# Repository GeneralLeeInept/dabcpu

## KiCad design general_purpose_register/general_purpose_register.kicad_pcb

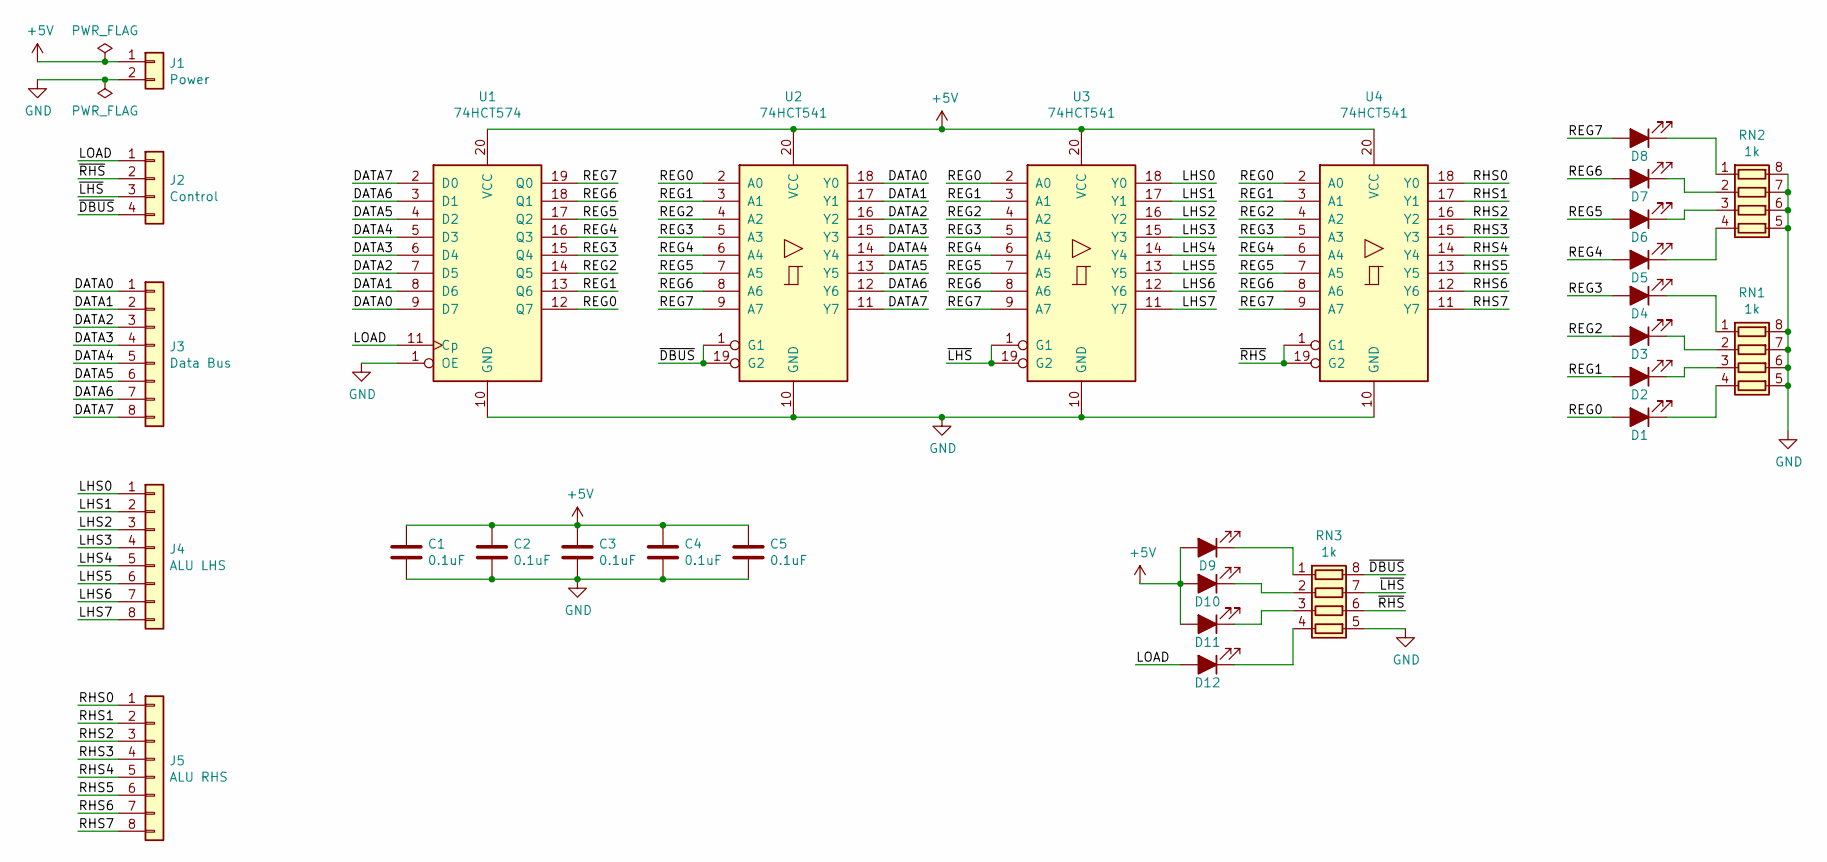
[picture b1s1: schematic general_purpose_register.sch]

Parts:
C1, C2, C3, C4, C5: 0.1uF; C_0805_2012Metric_Pad1.18x1.45mm_HandSolder
D1, D2, D3, D4, D5, D6, D7, D8, D9, D10, D11, D12: LED_ALT; LED_0805_2012Metric_Pad1.15x1.40mm_HandSolder
J1: Power; PinHeader_1x02_P2.54mm_Vertical
J2: Control; PinHeader_1x04_P2.54mm_Vertical
J3: Data Bus; PinHeader_1x08_P2.54mm_Vertical
J4: ALU LHS; PinHeader_1x08_P2.54mm_Vertical
J5: ALU RHS; PinHeader_1x08_P2.54mm_Vertical
RN1, RN2, RN3: 1k; R_Array_Convex_4x1206
U1: 74HCT574; SOIC-20W_7.5x12.8mm_P1.27mm; digikey 1727-2856-1-ND
U2, U3, U4: 74HCT541; SOIC-20W_7.5x12.8mm_P1.27mm; digikey 1727-6357-1-ND

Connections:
+5V: C1.1, C2.1, C3.1, C4.1, C5.1, D9.2 (A), D10.2 (A), D11.2 (A), J1.1, U1.20 (VCC), U2.20 (VCC), U3.20 (VCC), U4.20 (VCC)
/DATA0: J3.1, U1.9 (D7), U2.18 (Y0)
/DATA1: J3.2, U1.8 (D6), U2.17 (Y1)
/DATA2: J3.3, U1.7 (D5), U2.16 (Y2)
/DATA3: J3.4, U1.6 (D4), U2.15 (Y3)
/DATA4: J3.5, U1.5 (D3), U2.14 (Y4)
/DATA5: J3.6, U1.4 (D2), U2.13 (Y5)
/DATA6: J3.7, U1.3 (D1), U2.12 (Y6)
/DATA7: J3.8, U1.2 (D0), U2.11 (Y7)
/LHS0: J4.1, U3.18 (Y0)
/LHS1: J4.2, U3.17 (Y1)
/LHS2: J4.3, U3.16 (Y2)
/LHS3: J4.4, U3.15 (Y3)
/LHS4: J4.5, U3.14 (Y4)
/LHS5: J4.6, U3.13 (Y5)
/LHS6: J4.7, U3.12 (Y6)
/LHS7: J4.8, U3.11 (Y7)
/LOAD: D12.2 (A), J2.1, U1.11 (Cp)
/REG0: D1.2 (A), U1.12 (Q7), U2.2 (A0), U3.2 (A0), U4.2 (A0)
/REG1: D2.2 (A), U1.13 (Q6), U2.3 (A1), U3.3 (A1), U4.3 (A1)
/REG2: D3.2 (A), U1.14 (Q5), U2.4 (A2), U3.4 (A2), U4.4 (A2)
/REG3: D4.2 (A), U1.15 (Q4), U2.5 (A3), U3.5 (A3), U4.5 (A3)
/REG4: D5.2 (A), U1.16 (Q3), U2.6 (A4), U3.6 (A4), U4.6 (A4)
/REG5: D6.2 (A), U1.17 (Q2), U2.7 (A5), U3.7 (A5), U4.7 (A5)
/REG6: D7.2 (A), U1.18 (Q1), U2.8 (A6), U3.8 (A6), U4.8 (A6)
/REG7: D8.2 (A), U1.19 (Q0), U2.9 (A7), U3.9 (A7), U4.9 (A7)
/RHS0: J5.1, U4.18 (Y0)
/RHS1: J5.2, U4.17 (Y1)
/RHS2: J5.3, U4.16 (Y2)
/RHS3: J5.4, U4.15 (Y3)
/RHS4: J5.5, U4.14 (Y4)
/RHS5: J5.6, U4.13 (Y5)
/RHS6: J5.7, U4.12 (Y6)
/RHS7: J5.8, U4.11 (Y7)
/~DBUS: J2.4, RN3.8 (R1.2), U2.1 (G1), U2.19 (G2)
/~LHS: J2.3, RN3.7 (R2.2), U3.1 (G1), U3.19 (G2)
/~RHS: J2.2, RN3.6 (R3.2), U4.1 (G1), U4.19 (G2)
GND: C1.2, C2.2, C3.2, C4.2, C5.2, J1.2, RN1.5 (R4.2), RN1.6 (R3.2), RN1.7 (R2.2), RN1.8 (R1.2), RN2.5 (R4.2), RN2.6 (R3.2), RN2.7 (R2.2), RN2.8 (R1.2), RN3.5 (R4.2), U1.1 (OE), U1.10 (GND), U2.10 (GND), U3.10 (GND), U4.10 (GND)
unnamed: D1.1 (K), RN1.4 (R4.1)
unnamed: D2.1 (K), RN1.3 (R3.1)
unnamed: D3.1 (K), RN1.2 (R2.1)
unnamed: D4.1 (K), RN1.1 (R1.1)
unnamed: D5.1 (K), RN2.4 (R4.1)
unnamed: D6.1 (K), RN2.3 (R3.1)
unnamed: D7.1 (K), RN2.2 (R2.1)
unnamed: D8.1 (K), RN2.1 (R1.1)
unnamed: D9.1 (K), RN3.1 (R1.1)
unnamed: D10.1 (K), RN3.2 (R2.1)
unnamed: D11.1 (K), RN3.3 (R3.1)
unnamed: D12.1 (K), RN3.4 (R4.1)

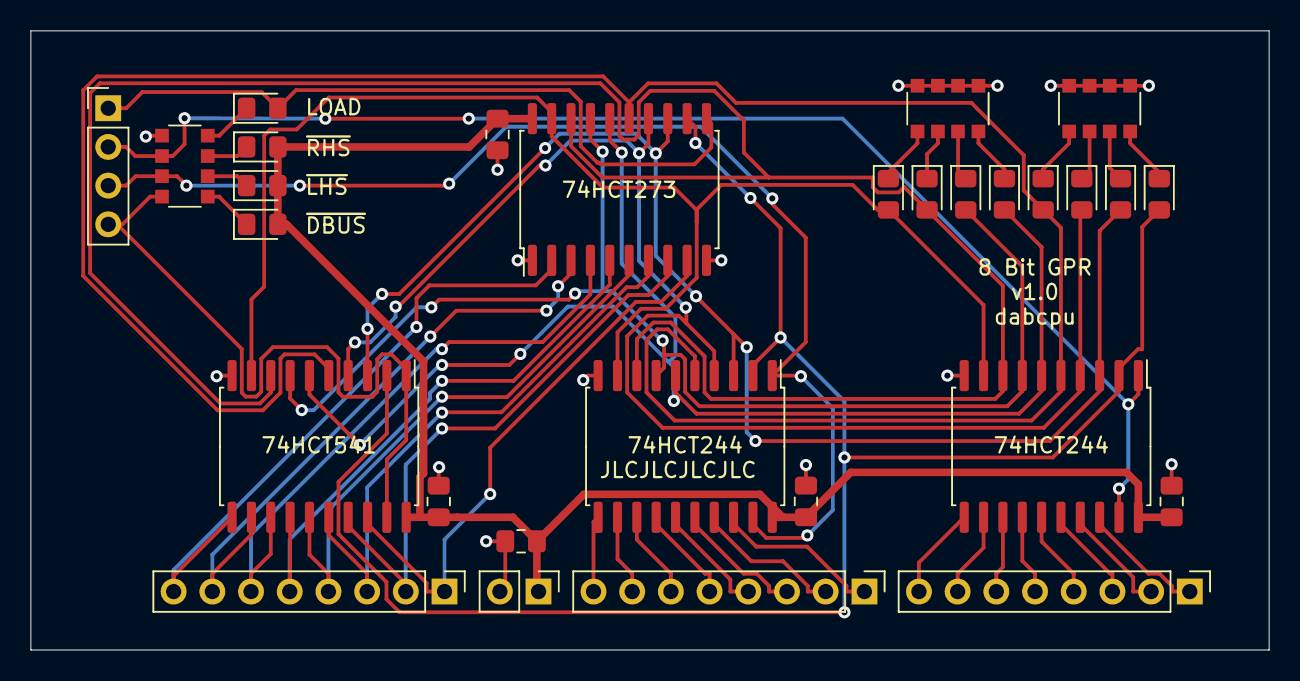
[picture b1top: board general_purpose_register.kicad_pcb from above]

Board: 2 copper layers, 81.3 x 40.6 mm, 29 parts (0 on the bottom side), 50 nets.

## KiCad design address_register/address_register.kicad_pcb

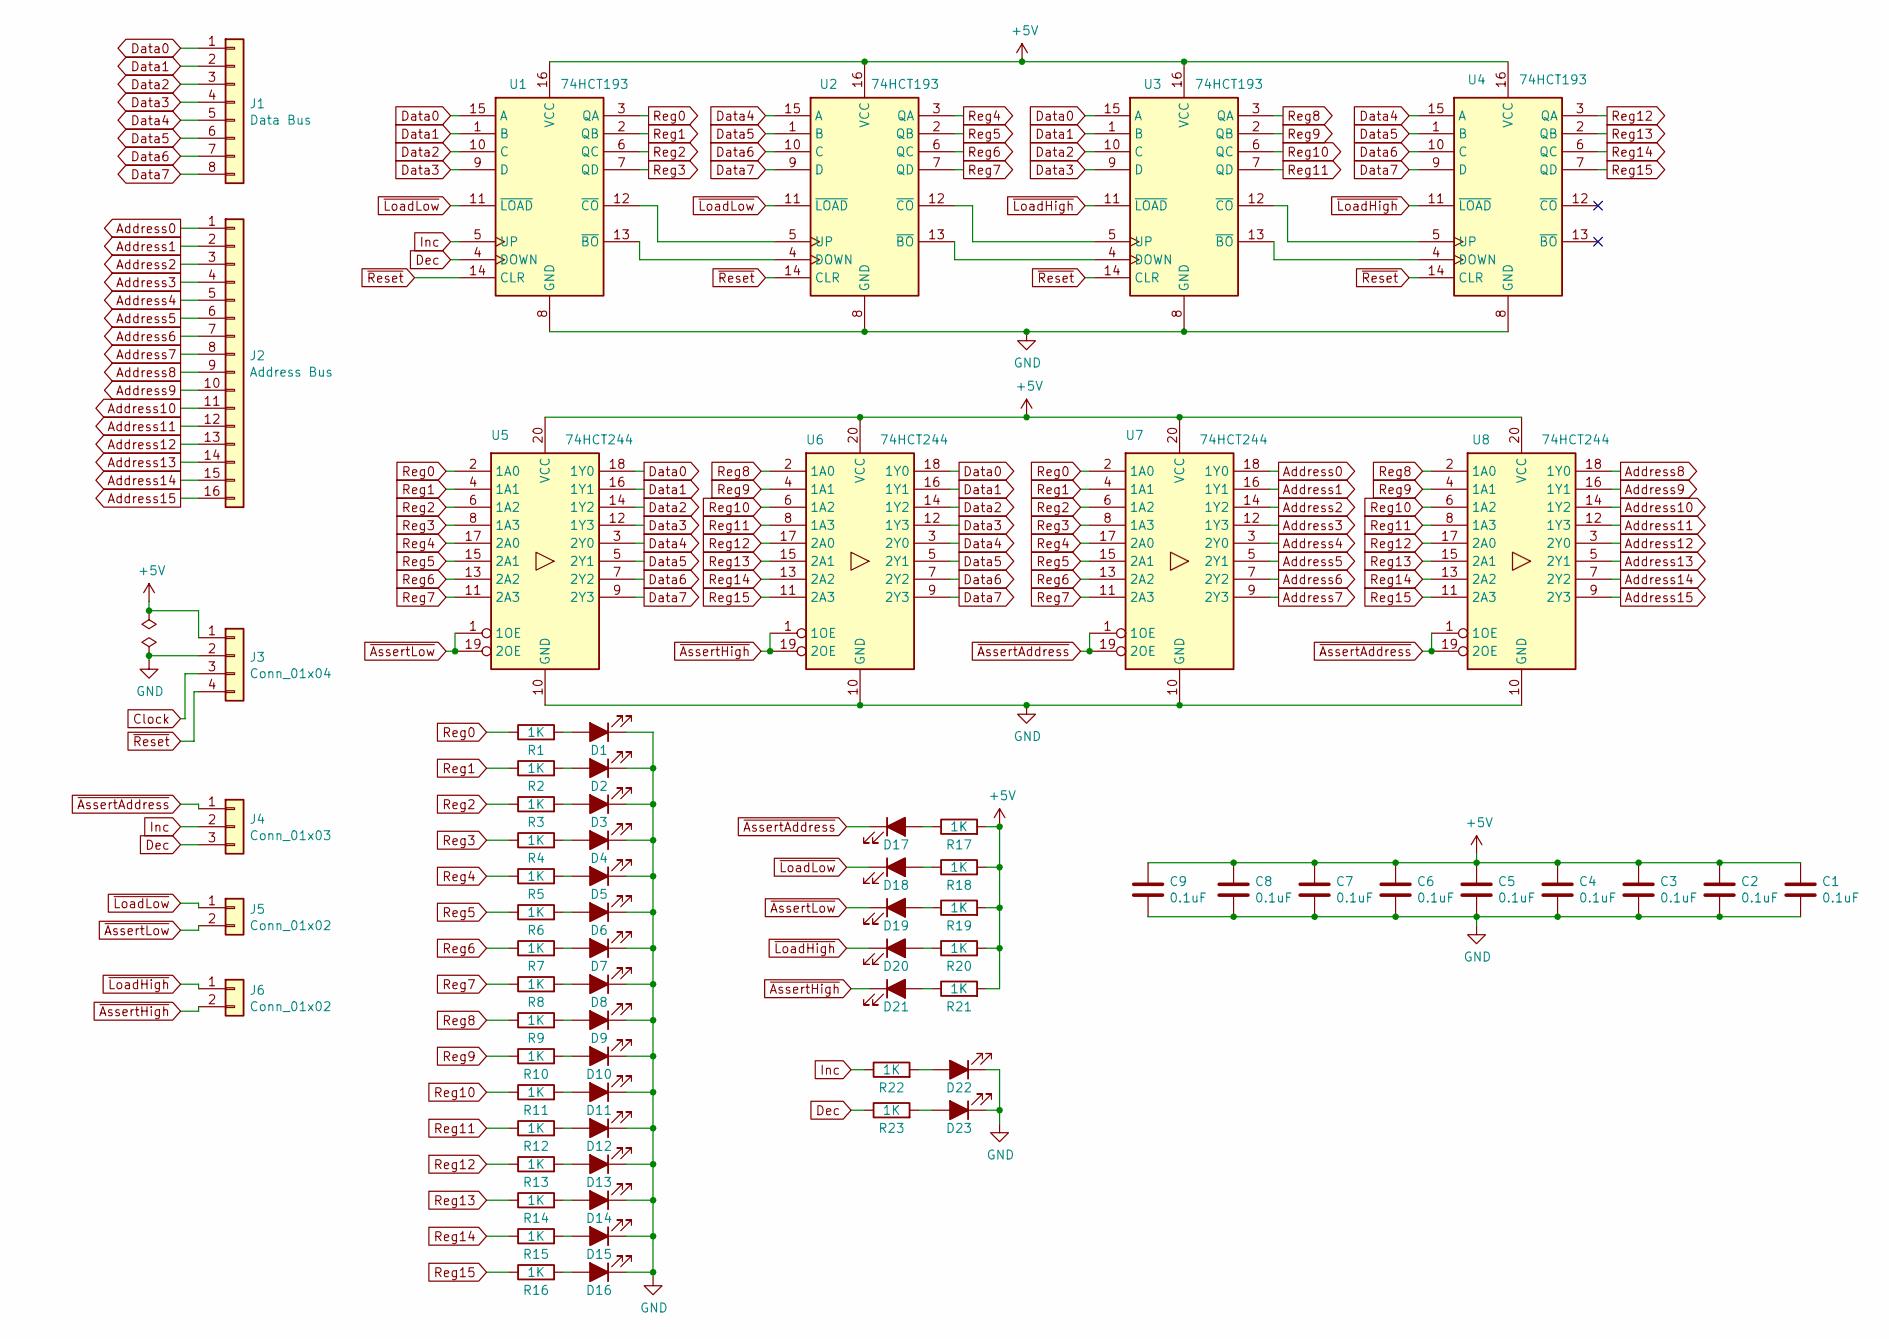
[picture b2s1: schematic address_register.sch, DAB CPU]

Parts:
C1, C2, C3, C4, C5, C6, C7, C8, C9: 0.1uF; C_0805_2012Metric_Pad1.18x1.45mm_HandSolder
D1, D2, D3, D4, D5, D6, D7, D8, D9, D10, D11, D12, D13, D14, D15, D16, D17, D18, D19, D20, D21, D22, D23: LED_ALT; LED_0805_2012Metric_Pad1.15x1.40mm_HandSolder
J1: Data Bus; PinHeader_1x08_P2.54mm_Vertical
J2: Address Bus; PinHeader_1x16_P2.54mm_Vertical
J3: Conn_01x04; PinHeader_1x04_P2.54mm_Vertical
J4: Conn_01x03; PinHeader_1x03_P2.54mm_Vertical
J5, J6: Conn_01x02; PinHeader_1x02_P2.54mm_Vertical
R1, R2, R3, R4, R5, R6, R7, R8, R9, R10, R11, R12, R13, R14, R15, R16, R17, R18, R19, R20, R21, R22, R23: 1K; R_0805_2012Metric_Pad1.20x1.40mm_HandSolder
U1, U2, U3, U4: 74HCT193; SOIC-16_3.9x9.9mm_P1.27mm; digikey 1727-5967-1-ND
U5, U6, U7, U8: 74HCT244; SOIC-20W_7.5x12.8mm_P1.27mm; PartNo SN74HCT244DWR; digikey 296-1207-1-ND

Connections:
+5V: C1.1, C2.1, C3.1, C4.1, C5.1, C6.1, C7.1, C8.1, C9.1, J3.1, R17.2, R18.2, R19.2, R20.2, R21.2, U1.16 (VCC), U2.16 (VCC), U3.16 (VCC), U4.16 (VCC), U5.20 (VCC), U6.20 (VCC), U7.20 (VCC), U8.20 (VCC)
Address0: J2.1, U7.18 (1Y0)
Address1: J2.2, U7.16 (1Y1)
Address2: J2.3, U7.14 (1Y2)
Address3: J2.4, U7.12 (1Y3)
Address4: J2.5, U7.3 (2Y0)
Address5: J2.6, U7.5 (2Y1)
Address6: J2.7, U7.7 (2Y2)
Address7: J2.8, U7.9 (2Y3)
Address8: J2.9, U8.18 (1Y0)
Address9: J2.10, U8.16 (1Y1)
Address10: J2.11, U8.14 (1Y2)
Address11: J2.12, U8.12 (1Y3)
Address12: J2.13, U8.3 (2Y0)
Address13: J2.14, U8.5 (2Y1)
Address14: J2.15, U8.7 (2Y2)
Address15: J2.16, U8.9 (2Y3)
Data0: J1.1, U1.15 (A), U3.15 (A), U5.18 (1Y0), U6.18 (1Y0)
Data1: J1.2, U1.1 (B), U3.1 (B), U5.16 (1Y1), U6.16 (1Y1)
Data2: J1.3, U1.10 (C), U3.10 (C), U5.14 (1Y2), U6.14 (1Y2)
Data3: J1.4, U1.9 (D), U3.9 (D), U5.12 (1Y3), U6.12 (1Y3)
Data4: J1.5, U2.15 (A), U4.15 (A), U5.3 (2Y0), U6.3 (2Y0)
Data5: J1.6, U2.1 (B), U4.1 (B), U5.5 (2Y1), U6.5 (2Y1)
Data6: J1.7, U2.10 (C), U4.10 (C), U5.7 (2Y2), U6.7 (2Y2)
Data7: J1.8, U2.9 (D), U4.9 (D), U5.9 (2Y3), U6.9 (2Y3)
Dec: J4.3, R23.1, U1.4 (DOWN)
GND: C1.2, C2.2, C3.2, C4.2, C5.2, C6.2, C7.2, C8.2, C9.2, D1.1 (K), D2.1 (K), D3.1 (K), D4.1 (K), D5.1 (K), D6.1 (K), D7.1 (K), D8.1 (K), D9.1 (K), D10.1 (K), D11.1 (K), D12.1 (K), D13.1 (K), D14.1 (K), D15.1 (K), D16.1 (K), D22.1 (K), D23.1 (K), J3.2, U1.8 (GND), U2.8 (GND), U3.8 (GND), U4.8 (GND), U5.10 (GND), U6.10 (GND), U7.10 (GND), U8.10 (GND)
Inc: J4.2, R22.1, U1.5 (UP)
unnamed: D1.2 (A), R1.2
unnamed: D2.2 (A), R2.2
unnamed: D3.2 (A), R3.2
unnamed: D4.2 (A), R4.2
unnamed: D5.2 (A), R5.2
unnamed: D6.2 (A), R6.2
unnamed: D7.2 (A), R7.2
unnamed: D8.2 (A), R8.2
unnamed: D9.2 (A), R9.2
unnamed: D10.2 (A), R10.2
unnamed: D11.2 (A), R11.2
unnamed: D12.2 (A), R12.2
unnamed: D13.2 (A), R13.2
unnamed: D14.2 (A), R14.2
unnamed: D15.2 (A), R15.2
unnamed: D16.2 (A), R16.2
unnamed: D17.2 (A), R17.1
unnamed: D18.2 (A), R18.1
unnamed: D19.2 (A), R19.1
unnamed: D20.2 (A), R20.1
unnamed: D21.2 (A), R21.1
unnamed: D22.2 (A), R22.2
unnamed: D23.2 (A), R23.2
unnamed: U1.12 (~CO), U2.5 (UP)
unnamed: U1.13 (~BO), U2.4 (DOWN)
unnamed: U2.12 (~CO), U3.5 (UP)
unnamed: U2.13 (~BO), U3.4 (DOWN)
unnamed: U3.12 (~CO), U4.5 (UP)
unnamed: U3.13 (~BO), U4.4 (DOWN)
Reg0: R1.1, U1.3 (QA), U5.2 (1A0), U7.2 (1A0)
Reg1: R2.1, U1.2 (QB), U5.4 (1A1), U7.4 (1A1)
Reg2: R3.1, U1.6 (QC), U5.6 (1A2), U7.6 (1A2)
Reg3: R4.1, U1.7 (QD), U5.8 (1A3), U7.8 (1A3)
Reg4: R5.1, U2.3 (QA), U5.17 (2A0), U7.17 (2A0)
Reg5: R6.1, U2.2 (QB), U5.15 (2A1), U7.15 (2A1)
Reg6: R7.1, U2.6 (QC), U5.13 (2A2), U7.13 (2A2)
Reg7: R8.1, U2.7 (QD), U5.11 (2A3), U7.11 (2A3)
Reg8: R9.1, U3.3 (QA), U6.2 (1A0), U8.2 (1A0)
Reg9: R10.1, U3.2 (QB), U6.4 (1A1), U8.4 (1A1)
Reg10: R11.1, U3.6 (QC), U6.6 (1A2), U8.6 (1A2)
Reg11: R12.1, U3.7 (QD), U6.8 (1A3), U8.8 (1A3)
Reg12: R13.1, U4.3 (QA), U6.17 (2A0), U8.17 (2A0)
Reg13: R14.1, U4.2 (QB), U6.15 (2A1), U8.15 (2A1)
Reg14: R15.1, U4.6 (QC), U6.13 (2A2), U8.13 (2A2)
Reg15: R16.1, U4.7 (QD), U6.11 (2A3), U8.11 (2A3)
~AssertAddress: D17.1 (K), J4.1, U7.1 (1OE), U7.19 (2OE), U8.1 (1OE), U8.19 (2OE)
~AssertHigh: D21.1 (K), J6.2, U6.1 (1OE), U6.19 (2OE)
~AssertLow: D19.1 (K), J5.2, U5.1 (1OE), U5.19 (2OE)
~LoadHigh: D20.1 (K), J6.1, U3.11 (~LOAD), U4.11 (~LOAD)
~LoadLow: D18.1 (K), J5.1, U1.11 (~LOAD), U2.11 (~LOAD)
~Reset: J3.4, U1.14 (CLR), U2.14 (CLR), U3.14 (CLR), U4.14 (CLR)

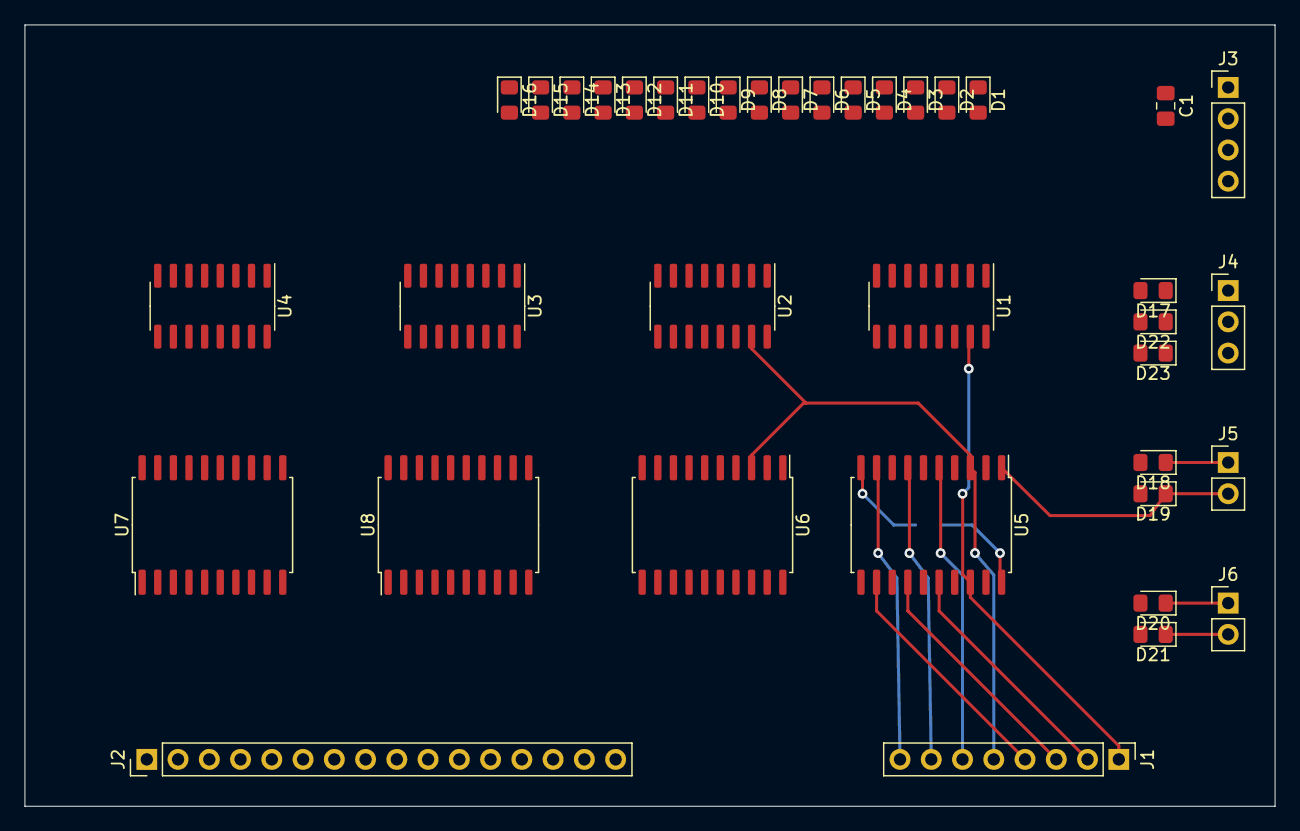
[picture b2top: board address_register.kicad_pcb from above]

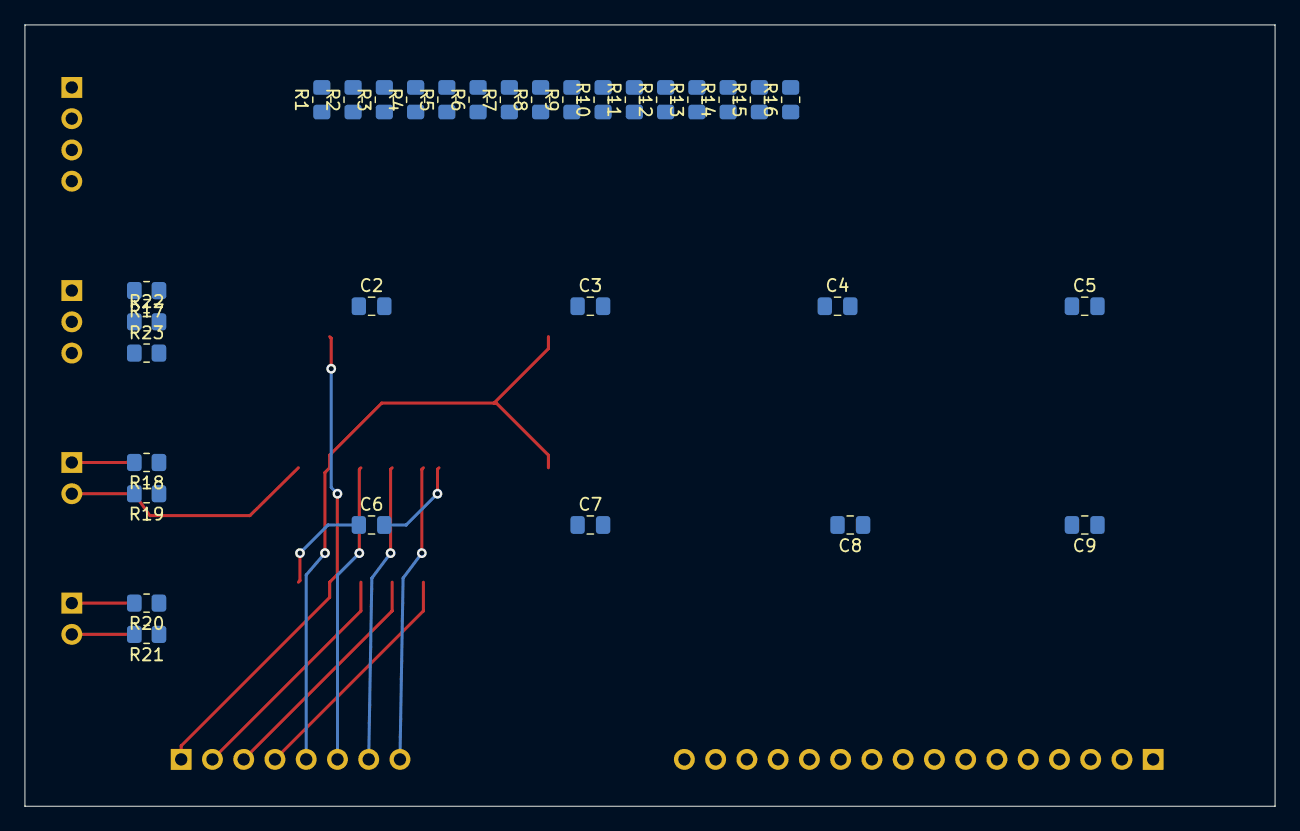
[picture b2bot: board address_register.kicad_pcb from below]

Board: 2 copper layers, 101.6 x 63.5 mm, 69 parts (31 on the bottom side), 79 nets.

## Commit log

2021-12-11 Rerouted for better ground plane.
